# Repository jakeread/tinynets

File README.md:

# Tiny Nets

TinyNets presents a networking strategy for distributed robotic control systems. Resilient Stateless Multipath Message Passing for Very Fast Very Small Messages: RSMMRVFVSM ... 

## Networked Control Systems (NCS)

The field of Networked Control Systems, or NCS, is unique from many other networking fields. NCS refers to any application where many devices are linked together to perform control of a physical system. They are common in robotics and avionics, where many sensors and actuators work together to perform a common goal (i.e. walking, stabilization, etc.), and in manufacturing, where machine degrees of freedom are linked to close positioning control loops, and where multiple machines are linked to coordinate material handling and production scheduling. 

Critically,
- In NCS, **total throughput is valued but not a key metric.** 
- Rather, message sizes are typically very small (between three and fifty bytes) and message delay time is the critical metric. Often, messages are only one packet in length.  
- **Determinism in Message Delivery Time is critical** - systems must guarantee that certain control loops 'close' within a defined set of time less they become unstable. 
- **Robustness is critical** - NCS should not contain any Single Points of Failure
- **Statelessness is critical** - NCS should not pause operation under any circumstances to re-converge on routing solutions, as this adds fatal indeterminism to message delivery. 

## The State of the Art in NCS

State of the art Networked Control Systems employ simple Switched Ethernet, or proprietary versions thereof, in order to route traffic. Hardware endpoints are fitted with an Ethernet PHY and are connected in a heirarchy of switches. Ethernet MAC addresses are used, and all routing takes place on Layer 2. 

Switched Ethernet has become the industry standard because of its relative interoperability and high speeds. Critically, the last 10 years has seen Switched Ethernet take up large portions of market share because it solves many problems associated with Fieldbusses. Most importantly, adding devices to a Fieldbus always caused a linear increase in message delivery time, as is not the case with Switched Ethernet.

## Dissatisfaction with Switched Ethernet

However, Switched Ethernet was not originally developed for Networked Control Systems, and many in industry have pointed out that it will not fulfill customer needs in the near- and long-term future.

In Switched Ethernet, because a Minimum Spanning Tree is created, nodes in a particular layer compete for link-time on the layer above. Message delay time increases linearly with the probability that peers are transmitting at the same time, and with the number of peers on that layer. 

In addition, Switched Ethernet contains Single Points of Failure, where a broken link or switch means that the network must re-run the Spanning Tree Protocol algorithm - a process that often takes seconds. Because Switched Ethernet graphs are highly heirarchical, it is often the case that failure on a single link can cause entire sections of the network to fail, or become unreachable. 

Device endpoints in NCS are scaling down in size and up in number. Requiring that each endpoint carries with it an RJ45 Magnetic Jack and Ethernet PHY is dubious, and sets a lower limit on the size and complexity that sensors and actuators in an NCS must possess. 

Switched Ethernet is non-programmable. I.E. Switches are black-box IC's and do not allow systems designers to arbitrarily add functions to a system on the networking layer. For example, many NCS designers would like to implement message priorities and load balancing, but this is not possible on Layer 2. 

# Constraints and Cost Functions for TinyNet

## Constraints

In the design of TinyNets, we operate under the following constraints:

- TinyNet should be trivially integrated on device endpoints. I.E. an endpoint should not require any additional hardware circuitry. This allows the network to scale down into micro-robotics applications.
- TinyNets should run entirely in C or C++ on the processors used on endpoints and routers, meaning that network protocols can be openly modified within an Autonomous System to perform application-specific tasks. TinyNets is Open Source Software.
- TinyNets should run with no global state. It should not have to re-converge on routing solutions in the face of broken or modified links, additions to the network, or changes in traffic patterns.

## Direct Comparisons

It will be difficult to perform one-to-one comparisons between our network and the state of the art, as we are proposing a completely new solution in response to problems in NCS that we believe cannot be addressed with incremental modifications to existing technologies. 

## Proving our Merit

However, we can offer analysis as to why we believe our approach is substantially better than current offerings - or has a better problem-solution fit than other technologies. 

**Realtime / Convergence Free Multipath Routing in a Distance-Vector Routing Protocol**
- Existing Multipath Routing Technologies offer multipath routing (which eliminates the switching-bottleneck issues associated with switched ethernet), however, they do so using link-state routing that requires each router to share common knowledge about the complete network graph. In the face of link outages or router failures, networks must re-converge - a process that interrupts flows and causes massive increases, or complete failures, in message deliveries. For example
 - ECMP (Equal Cost Multipath Routing): more of a tool than an actual strategy; simply considers multiple paths when there are multiple best paths, i.e. load balancing mechanism
 - OSPF (Open Shortest Path First): Computes shortest path tree using Dijstra -- must know entire graph; wikipedia states convergence time is on the order of seconds (links to Cisco default parameters that set timeouts to be multiple seconds); specifically for Ethernet and offers a multipath version
 - SPB (Shortest Path Bridging): allows multiple equal cost paths and claims network is unaffected when a node fails except for the path(s) affected by the node failure, i.e. still cannot find another path if there is a unique shortest path containing a broken link
 - TRILL (TRansparent Interconnect of Lots of Links): must know entire graph, otherwise extremely similar to our protocol (uses hop counts and has similar flooding procedure); operates in Layer 2 and uses Fabric Shortest Path First (FSPF) to calculate alternate routes in node failure scenarios

We seek to demonstrate that these re-convergence times would cause operational failure in NCS, thus eliminating ECMP and OSPF as possible solutions to the NCS problem. 

The three protocols in question (OSPF, SPB, TRILL) require knowing the entire graph to perform a global shortest path calculation. All three of them allow for multipath consideration when there are multiple best paths. 200 ms seems to be the lower bound on convergence times as FSPF is quoted to having as good as 200 ms convergence time in the book "IBM SAN Solution Design Best Practices for VMWare" book. The vanilla OSPF protocol that Cisco offers indicates around an order second convergence time while optimized versions offer similar timing to FSPF (see paper).

200 ms sounds like a reasonable convergence time (and is quoted as being extremely fast) so to prove our merit, we need to demonstrate systems that do not have multiple shortest paths using the protocols above. This should highlight the main benefit of our protocol, that being the capability to perform real time alternate path calculations in a reasonable amount of time.

We propose designing multiple experiments to showcase the benefit of our protocol:
1. Grid structure network - test latency of corner communication and traffic of network during node failure. This test will serve as a control since there will be many shortest paths (if hop count is used as the metric).
2. Ring structure network - we already have graphs for this from the other protocol and it will demonstrate the speed at which each protocol finds the only other path in the event of a node failure.
3. Mesh network - fully connected network that will test our network utilization (ensure ringing doesn't happen or is at least bounded tightly). Test the latency of cross network communication in the event of a node failure. We should expect to see minimal decision time in our protocol and minimal flooding.

**Avoiding Switching Bottlenecks with Multipath Routing**
- In a careful literature review and analysis, we will show that Layer-2 Solutions (switched ethernet) necessarily cause switching bottlenecks that create Single Points of Failure and increases in Message Delivery Times to NCS.

From [worst-case-packet-delay-time paper], we know that the worst case communication delay over Ethernet occurs when the number of frames attempting to communicate over a single switch is the greatest. For example, when a spanning tree organizes itself such that 24 stations are connected to a single switching hub, a typical 144-bit message with a bit time of 0.1 us would take more than 1.5 ms to finish sending a single packet from all stations. If the packets could be interconnected without the tree structure required by Ethernet/IP, transmission time could be brought down to just over 300 us. 

The above figure compares strategies for reducing communication time. The parameter which has the largest parameter is the number of frames being communicated over a single switch. This is to be expected, since that parameter will have a multiplicative effect on the queuing delay. By sacrificing the spanning tree topology and leveraging multipath routing without the added processing delays and stateful nature of ECMP or other link-state routing methodologies, we will drastically reduce frame count and, therefore, communication time.

## Our Cost Functions

In addition to proving our merit with a careful literature review, we can devise cost functions and metrics to measure our development. These include:

**Optimal Network Utilization**
- Using logic analyzers and in-system programming to track message delay times and routes, we will measure the efforts of TinyNet routing policies to optimize network utilization and minimize message delivery times.

**Deterministic Packet Delivery in the face of Increasing Network Traffic**
- Similarly, we will measure TinyNet performance (in terms of message delivery times) as total network traffic increases.

**Robust Packet Delivery in the face of Lost Links and Routers**
- We will demonstrate TinyNet adaptively re-routing messages as links are cut, or routers are removed from the network graph, without any network re-convergence.  

# Key Contributions

A strategy for stateless multipath routing that increases message delivery time determinism and network robustness.

A real-time cost function, using next-hop buffer size (i.e. busyness metric) as well as historical hop-count for per-packet dynamic re-routing, that increases packet delivery-time determinism. 

A software-defined network architecture for arbitrary implementation in any embedded system, where computing, physical space, and time is limited. 

# Direct Applications

#### Micro-Robotics with Complexity

NCS via Switched Ethernet is impossible to drive into micro-robotics, where a single RJ45 Jack is larger than many endpoints. TinyNets provides a strategy and implementable software stack that will allow roboticists to bring adaptable, real-time networking to highly interconnected and complicated robotic systems. 

#### Avionics

Existing NCS are prone to Single Points of Failure and rapidly scaling complexity and cost. These is the bane of aircraft systems designers. We believe that TinyNet can offer avionics networks a robust, simple, and easily extensible strategy for the design and implementation of NCS in aircraft control systems. 

##### Open Source Reconfigurable Hardware Systems

In particular, hardware design for embedded systems in the open source (i.e. non-expert) realm. We want to offer a networking solution that allows open source designers to easily integrate their systems. We take the example of a proliferation of 3D Printer Control systems, none of which interop, and the interfaces between are a PITA. Expand on this. 

# TinyNet Protocol & Architecture

We develop a router, protocol and implementation of a network that: 
 - Implements a Multipath Distance-Vector Routing Protocol
 - Does Realtime Route Selection
 - Does Automatic, Convergence-free Route Discovery and Optimization
 - Is robust in the face of link losses and router failures
 - Can be arbitrarily implemented in software on numerous microcontrollers

## Addressing 
    - 10-bit address (1024 Unique in System, scalable by systems designers at the cost of larger packet size)
    - Addresses are assigned in software (Ethernet: Hardware Addresses)
    - Can be location-based (e.g. first five MSBs correspond to x, last five correspond to y)

## Packet Structure  

| Type | 8 Bits | 10 Bits | 6 Bits | 10 Bits | 6 Bits | N Bytes | CRC |  
| --- | --- | --- | --- | --- | --- | --- | --- | 
| Standard: | 255 | Dest. | Hop Count | Src. | # Bytes | Payload … | CRC |  
| ACK: | 253 | Dest. | Hop Count | Src. | x | x | CRC |  
| Buffer Length: | [0 - 251] | x | x | x | x | x | x |  

* previously-flooded Standard Packets have start delimiter 254
* previously-flooded Acks have start delimiter 252

## Routing Rules

On Packet Received:
```swift

if the packet is not a buffer update:
	update the LUT using packet src. and hop count

if packet is standard:
    if I am destination:
        process data in packet
		reply with ACK
    else:
		increment hop count
        if LUT has destination address:
            send packet to port which minimizes C(hops, buffer) = hops + \lambda*buffer over all ports
        else:
            send packet to all ports as standard flood

elseif packet is ack:
    if I am destination:
        process acknowledgement
    else:
        increment hop count
        if LUT has destination address:
            send packet to port which minimizes C(hops, buffer) = hops + \lambda*buffer over all ports
        else:
            send packet to all ports as ack flood

elseif packet is standard flood:
	remove packet src. from LUT at that port if it exists
	if I have not yet seen this flood:
		if I am destination:
			process data in packet
			reply with ACK
		else:
			increment hop count
			if LUT has destination address:
				send packet to port which minimizes C(hops, buffer) = hops + \lambda*buffer as standard packet
			else:
				send packet to all ports except one from which it was received

elseif packet is ack flood
    remove packet src. from LUT at that port if it exists
    if I am destination:
        process acknowledgement
    else:
		increment hop count
        if LUT has destination address:
            send packet to port which minimizes C(hops, buffer) = hops + \lambda*buffer as standard ACK
        else:
            send packet to all ports except one from which it was received

else:
    write buffer depth to LUT

```

## Routing Table

The routing table (or lookup table, LUT) consists of rows of:  

| Destination | Seen on Ports | Min. Hopcount Recorded on Port | Port buffer size |

This is different from standard Ethernet routing tables:

| Ports | Destinations seen on Port |

Because it includes the current port buffer size and number of hops as part of the table entry, allowing for a more robust cost function for use in the path planning algorithm. 

## Buffer Depth Updates
Send buffer depth on all ports every q seconds, and every time a packet leaves or arrives

## Announcements 
New arrivals to network do not announce, they simply begin transmitting. Their addresses are recoreded in surrounding switches' tables on their first packet-out.

## Withdrawals
Buffer Depth Updates are Periodic as well as event-based (on buffer-depth change). When no BDU is heard within a 250ms (or other setting) window, the node is considered withdrawn.

# Hardware

See /circuit 
See /embedded 

# Next Steps

Presents a good option for wired routing over robust networks, with some complexity pushed into the nodes. Only really advantageous when we want to be able to re-route messages upstream in order to move around bottlenecks. TN does load-balancing without thinking about it... other approaches would require some implementation. Perhaps there's a learning function for network path planning & routing? 

If we include flows, needs per-flow, not per-packet, routing - if we are going to hop about per buffers etc. 

Wants a C API for packetizing streams / flows. 

Still some question about duplicate message arrivals after message? OR don't packetize flows - add source -> destination 0-255 counter, only take next in this series. 

TN wins over the blissfully simple APA when we want a *very big* network, say, want 1,000,000 objects to individually address 1,000,000 objects. Here we also need to introduce heirarchichal addressing. 

'Napoleon's Messenger' 

APA is *loads* simpler to implement on FPGA

# Reading

#### Networked Control Systems
Ethernet in Networked Control, advantages and drawbacks.  
See especially  
**/litreview/papers/network-control-systems/survey-on-realtime-via-ethernet**  
**/litreview/papers/network-control-systems/the-emergence-of-networked-controls**  

##### Packet Delivery Times in the face of Increasing Network Traffic

~ plot w/ x-axis is # nodes, transmitting at some % of time, y axis is per-packet delivery time ~
~ graph is single branch / spanning tree

Critically, adding multi-path to the graph above decreases the slope of this plot. Twice the total link-time on the layer above is available, or Nx, where N is the number of nodes added to the next. 

* state of the art for this? there is lit review to do here - look up TRILL and SPB (shortest path bridging). Much of it comes from Data Center Networks. 
 - https://datacenteroverlords.com/2011/08/19/multi-path-ethernet-the-flying-cars-of-the-data-center/ 
 - http://ieeexplore.ieee.org/stamp/stamp.jsp?arnumber=6888840
 - https://en.wikipedia.org/wiki/Equal-cost_multi-path_routing
 - https://infoscience.epfl.ch/record/231114/files/main_nr.pdf

Also critically, *it seems that, in a cursory overview* many multi-path techniques in use today basically do dynamic spanning-tree rebuilds. These spanning-tree rebuilds have long convergence times (162ms is excitingly fast). 

However, to increase determinism routes need to be chosen dymanically - so that *very short timescale* changes can be made to a packet, mid-network-traverse, to route around busy switches. Of interest is finding evidence that this is not done in any existing system.

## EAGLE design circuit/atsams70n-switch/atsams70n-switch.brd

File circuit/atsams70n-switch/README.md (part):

# A Router for TinyNet

## Why

This is board for switching UART signals in TinyNet. I wanted to keep some track of what I was doing, while I was doing it. So here it is.

Originally, I had developed a switch on the XMEGA platform. I wanted to get into something a bit heavier duty, as I thought a really neat trick would be to out-perform switched ethernet, outright (for network control systems, not for datacenters). I think that in ARM chips there was enough speed to do this. Maximum UART bitrate is a function of the core clock speed (and in this case, the peripheral clock speed). I went straight to the 300MHz ATSAMx70 chips (M7 cores).

Now, being more prudent I would do some tests with these chips first, but I'm not going to. This is foolish, I know that. Max UART on the ATSAMS70 is clk/16, so 18.75Mbps. It's not huge (relative ethernet), but it's fast enough for realtime small messages on small systems. In any case, I think the question is about system architecture more than it is about outright performance at this point.

I also think that, for pure switching, an FPGA or PSOC would be a better answer. It probably is. I want to experiment with those during Networks week in [how to make](http://fab.cba.mit.edu/classes/863.17/CBA/people/jakeread/).

However, I also want my network switches to double-duty as motor controllers, sensor interfaces, etc - do general embedded-stuff. In another world, where infinite time exists, I would put FPGAs on board with a processor. With the FPGA comes a chance to invent a whole new PHY - w/ 'co-clocking' and auto-maxing bitrates, which is something I am still really interested in implementing, but there are also machines to build. I leave that experiment for another bench.

## The Chip

First order was picking the right Microcontroller for the job. I want a lot of things, and I expect this chip to become the heart of *much* of the work I'll do during the next two years, so the datasheet stakes have never been so high.

**I want a chip with: **
 - 5+ uarts
 - Big Clock Speed
 - DMA (direct memory access - peripherals write right into memory)
 - PWM's
 - ADC's
 - I2C
 - SPI
 - PIO (parallel input / output) is really exciting for communication

##### M7's

I ended up looking through Atmel's M4 and M7 Series of chips. These seem reasonably priced (actually cheap relative STM's). They're ARM, so the toolchain should be friendly to others. The M7's have a 300MHz clock that I'm getting childishly excited about.

My one issue is that they are a bit too fancy, and don't have exactly the peripherals I want. The XMEGAs have like 12 UARTS etc, the M7's max out at 5, even with 144 pins. 

I can also tell that programming these is going to be ... well ... less straightforward.

##### GO FOR
 - ATSAME70 - series - or ATSAMS70
  - E70 is 'industrial' - and S70 lacks an Ethernet Phy, but seems like it's way more popular...
 - oodles of peripherals
 - a chip you could drown in
 - 300MHz
 - did I mention peripherals?
 - $8 ... a good middle ground 

#### ATSAMS70N20
 - Exact PN  ATSAMS70N20A-AN 
 - N19: 512kb Flash, N20: 1024, N21: 2048
 - 300MHz
 - OOF: Need S70N-series for USART / SPI (has 100 pins :|)
 - Do LQFP for 14.5x14.5mm IC: TFBGA available, is 9x9mm
 - **Reads the datasheet**
  - print p. 1 -> 31 pins
  - print p. 77 -> 84 debug
  - p. 279 -> 346 clock / pmic
  - p. 346 -> 421 pio (gpio)
  - print p. 1093 -> 1117 uart
  - print p. 756 -> 788 spi
  - p. 831 -> 835 brief twi (i2c)
  - p. 964 - 968 brief usart
  - print p. 1178 -> 1186 -> 1282 pwm
  - p. 1283 -> 1288 afec (adc) brief
  - p. 158 -> 164 Power
  - p. 1554 -> 1574 Schematics

 - UART max clock is the Peripheral Clock or the PMC PCK - divided by 16. PMC PCK is an external clock, so UART clock can remain independent of processor clock.
 - So we can have (as measured) 22.8Mbps UART - into high-speed bouncy signal land. Exciting.

## Bonus Breakout

I want the following (or similar) pinouts coming off of the network node - to do *other stuff* with - i.e. motor control, sensing etc. Particularely, in a first rev of this board I am designing alongside my [bldc motor driver](https://gitlab.cba.mit.edu/jakeread/mkbldcdriver) project. 

 - 1x UART
 - 1x SPI w/ 4 cs, 1 for slave select
 - 1-2x i2c
 - 8-12x PWM, pairs three
 - all dac
 - 8-12 adc 

In the end, at this iteration, I have

 - 1 UART
 - 1 I2C (I2C and UART share one pin, so cannot be used at the same time)
 - 1 SPI w/ 2 Chip Selects
 - 1 USART w/ 2 Chip Selects (USART can be configured to do UART, or SPI, or a Clocked Serial line of your design)
 - 8 PWM's on 4 channels (hi/lo - this is designed for driving half bridges for motor control)
 - 4 Analog to Digital Converters (I am less pleased with this and want more...)
 - 3 Spare GPIO

Notes on this so far
 - More ADC's please
 - Pin headers could be split - to be breadboard friendly, and to offer some stability between layers

# Board Design

The first thing I did was to get into the datasheet. You can see that in the notes above. I am doing pinouts, figuring what I want on board. I am going to set this up as a kind of modular getdown, where the switch has a board interconnect, and I can build other PCBs w/ different hardwares to ride below. I.E motor controllers, sensor interfaces, human interfaces (!). Picking the set of pins I wanted to pull out of the chip was actually a bit painful. I'm sure I'll go through this more than once.

For JTAG Pinouts, I referenced the Tag-Connect footprint (available for download from Tag-Connect) and the ATSAM note here - http://www.atmel.com/webdoc/atmelice/atmelice.using_ocd_physical_jtag.html see Fig. 18. They match, so I don't have to do any footwork here. Nice.

I'm going to look at the board interconnect - to decide how many pins I want, I need to look at some applicaitons. I designed a Brushless Speed Controller last year, and this had me maxing out pins (for the first time!) I am going to use that as a starting point, and add I2C, which I know is common, and some other whatsits.

- 3v3
- GND (probably multiple - but want to keep clear signal / power GND separations. Alternately, spec for board-interconnect standoffs to do heavy ground lifting?
- PWM / GPIO x 18
- ADC x 6
- SPI x 2 x 2 CS (10)
- I2C (2) 
- DAC x 1
- Seems like 40 is right, ~ 41. 

I have been tempted to buy some fancy 'mezannine' connectors - but I ended up (after a few cycles) deciding to stick with a 2x20 2.54mm pitch connector. This way just about everyone will have access to the hardware, and I like that! It's also the same pitch as most IDC connectors, breadboards, etc - so hopping around between systems should be easy. I am almost tempted to split the pins a bit so that it could get right into a breadboard - or do an edge-style bb, but this seems like too much give in that direction.

OK, Here's my schematic

And the board

Fabricated

# Programming

It turns out this chip defaults to SWD, not JTAG. Should have read the datasheet more carefully. Also, I forgot to order the tag-connect for this number of pins...

### PIO

Here I am using the PIO peripheral (which also handles multiplexing for other peripherals) to turn one of my LED's on and off

```C

/*
 * atsams70-router.c
 *
 * Created: 11/18/2017 1:52:54 AM
 * Author : Jake
 */ 

#include "sam.h"

int main(void)
{
    // Initialize the SAM system
    SystemInit();
  
  // startup the PIOA peripheral clock - only necessary for Inputs and Interrupts
  PMC->PMC_PCER0 = 1 << ID_PIOA;
  
  // Peripheral Enable Register
  // Set PER to 1 at the pin to enable the PIO peripheral, 
  // set PDR (peripheral disable register) to 1 to clear that, opening the pin up for other peripherals (uart, etc)
  PIOA->PIO_PER |= PIO_PER_P28_Msk;
  // Output Enable Register
  PIOA->PIO_OER = PIO_PER_P28_Msk;

    while (1) 
    {
    // Clear Output Data Register (open drain)
    PIOA->PIO_CODR = PIO_PER_P28_Msk;
    // Set Output Data Register (voltage)
    PIOA->PIO_SODR = PIO_PER_P28_Msk;
    }
}

```

### ASF and Delay

ASF is Atmel Software Framework - from within Atmel Studio 7, ASF makes it easy to turn hardware peripherals on / off. It's kind of like a more-intense Arduino, in that it allows you to avoid digging in the Registers to do stuff. 

I'm more interested in doing the register digging, that way it seems easier to share and replicate code (no laundry list of dependencies to build and share) and it offers a future where I'm not in Atmel Studio 7, because *boo* proprietary software... 

But I do want a delay function, if only to test turning this light on and off. And, to be real, I think I want to use Atmel's USB CDC drivers as well - so that I can have a serial port enumerated real quick.

To use ASF, I also need to have a 'board' defined - this is like a hardware abstraction layer (HAL ... 9000). This is all explained as you go to ASF -> ASF Wizard in the top menu.

Now that I have this defined (a board) the build takes a LONG time. I am also getting a lot of errors, I think I'm going to start a new ASF project from scratch.

That's a lot better, I think.

To set the clock, I'm looking at 31.17 in the datasheet.

OK, F this, I went to http://asf.atmel.com/docs/latest/sam.drivers.mcan.quick_start.samv71_xplained_ultra/html/sysclk_quickstart.html and used ASF. I didn't need to configure anything other than setting up a #define BOARD_FREQ_MAINCK_XTAL (12000000UL) in my conf_board.h file. Nice. It's happily trucking at 300MHz now.

Here we are doing a GPIO Input

```C
#include <asf.h>

int main (void)
{
  /* Insert system clock initialization code here (sysclk_init()). */

  board_init();
  sysclk_init();
  
  /* Insert application code here, after the board has been initialized. */
  // startup the PIOA peripheral clock - only necessary for Inputs and Interrupts
  PMC->PMC_PCER0 = 1 << ID_PIOA;
  
  // Peripheral Enable Register
  // Set PER to 1 at the pin to enable the PIO peripheral,
  // set PDR (peripheral disable register) to 1 to clear that, opening the pin up for other peripherals (uart, etc)
  PIOA->PIO_PER |= PIO_PER_P28 | PIO_PER_P15;
  // Output Enable Register
  PIOA->PIO_OER = PIO_PER_P28;
  // Output Disable Register
  PIOA->PIO_ODR = PIO_PER_P15;
  // B1 pulls PA15 to GND

  while (1) {
    // Clear Output Data Register (open drain)
    if(PIOA->PIO_PDSR & PIO_PER_P15){
      PIOA->PIO_CODR = PIO_PER_P28;
    } else {
      PIOA->PIO_SODR = PIO_PER_P28;
    }
  }
}
```

### Ring Test

On the ring test, I'm getting a jumping value between 3.9MHz and 5.7MHz, 

pics

I'm hoping that the peripheral clock is set up on a different clock source than the main chip, as that's about 100 processor ticks between pin inversions, which is kind of unsatisfying.

So I couldn't find any way to change the clock frequency for PIO pins (although there are separate clocks for UART/USART and for the USB) but I did try putting the input on Port A and the Output on Port D, this put the ring back at 5.77MHz (173ns period). Here's the code I was running

```C

#include <asf.h>

// Ring is PD1 and PD2
// try PA17 and PD7

int main (void)
{
  /* Insert system clock initialization code here (sysclk_init()). */

  board_init();
  sysclk_init();
  
  /* Insert application code here, after the board has been initialized. */
  // startup the PIOA peripheral clock - only necessary for Inputs and Interrupts
  PMC->PMC_PCER0 = 1 << ID_PIOA;
  PMC->PMC_PCER0 = 1 << ID_PIOD; // to figure out what PCERx to write to, evaluate ID_yourperipheral, and look up on datashsheet p. 308 or 331
  
  // Peripheral Enable Register
  // Set PER to 1 at the pin to enable the PIO peripheral,
  // set PDR (peripheral disable register) to 1 to clear that, opening the pin up for other peripherals (uart, etc)
  PIOA->PIO_PER |= PIO_PER_P17; 
  PIOD->PIO_PER |= PIO_PER_P1 | PIO_PER_P2 | PIO_PER_P7;
  // Output Enable Register
  PIOA->PIO_OER = PIO_PER_P17;
  PIOD->PIO_OER = PIO_PER_P1;
  // Output Disable Register
  PIOD->PIO_ODR = PIO_PER_P7;
  PIOD->PIO_ODR = PIO_PER_P2;
  // B1 pulls PA15 to GND

  while (1) {
    if(REG_PIOD_PDSR & PIO_PER_P7){
      REG_PIOA_CODR = PIO_PER_P17;
    } else {
      REG_PIOA_SODR = PIO_PER_P17;
    }
  }
}
```

### UART

OK, now I'm going to go about setting up the UART, and see if I can push the bitrate *really* high.

Drove it up to 22.8 MHz (= 22.8 MBps) and saw some pretty gnar gnar ringing... I'm using a differential driver.

- pic 

I'm a little curious if it's maybe better to just drive right out of the logic level? It's a similar amount of bouncy... but with the differtial you take the difference, so ... in this photo Channel 2 (blue) is the logic level, and Channel 1 (yellow) is coming through the differential driver. I'm also curious if this can be chilled out with a tiny capacitor to ground... seems dubious. But in an exciting development I am into high speed signals land. Weeee. I would also be curious to see what a terminating resistor might do. I think, maybe not much? Update: basically this just attenuates the signal. My understanding is that terminating resistors (that span the + and - sides of the differential) are just meant to get rid of reflections.

- pic

Here's the barebones code I'm running

```C

#include <asf.h>

// P4LR is PD13
// Ring is PD1 and PD2
// try PA17 and PD7

// https://devel.rtems.org/browser/rtems/c/src/lib/libbsp/arm/atsam/libraries/libchip/source/uart.c?rev=e1eeb883d82ce218c2a9c754795cb3c86ac0f36d

int main (void)
{
  /* Insert system clock initialization code here (sysclk_init()). */

  board_init();
  sysclk_init();
  
  PMC->PMC_PCER0 = 1 << ID_PIOD;
  PIOD->PIO_OER = PIO_PER_P13;
  
  // P4RX -> URXD4 -> PD18
  // P4TX -> UTXD4 -> PD19
  
  PMC->PMC_PCER1 = 1 << 14; // ID is 44, position in this register is 12. datasheet p. 331 *shrugguy*
  
  // configure the pins for uart4
  // see datasheet 32.5.2 and 32.5.3
  PIOD->PIO_PDR = PIO_PER_P18; // see if we can combine once working
  PIOD->PIO_PDR = PIO_PER_P19;
  
  // we want peripheral c for both pins
  // abcdsr1 -> 0 abcdsr2 -> 1
  PIOD->PIO_ABCDSR[0] = ~PIO_PER_P18;
  PIOD->PIO_ABCDSR[0] = ~PIO_PER_P19;
  PIOD->PIO_ABCDSR[1] = PIO_PER_P18;
  PIOD->PIO_ABCDSR[1] = PIO_PER_P19;
  
  // set uart mode
  UART4->UART_MR = UART_MR_BRSRCCK_PERIPH_CLK | UART_MR_CHMODE_NORMAL;
  
  // set uart clock
  UART4->UART_BRGR = 1; // is selected clock / this*16
  
  // turn tx and rx on on the uart4 module
  UART4->UART_CR = UART_CR_TXEN | UART_CR_RXEN;

  while (1) {
    while(!(UART4->UART_SR & UART_SR_TXRDY)){
      PIOD->PIO_CODR = PIO_PER_P13;
    }
    PIOD->PIO_SODR = PIO_PER_P13;
    UART4->UART_THR = 85;
  }
}
```

OK, enough for that wakeup, now I'm going to try to boot the USB CDC driver. This is something I'm more stoked about, and the last key component to letting me know that these chips are going to generally work.

### USB CDC

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
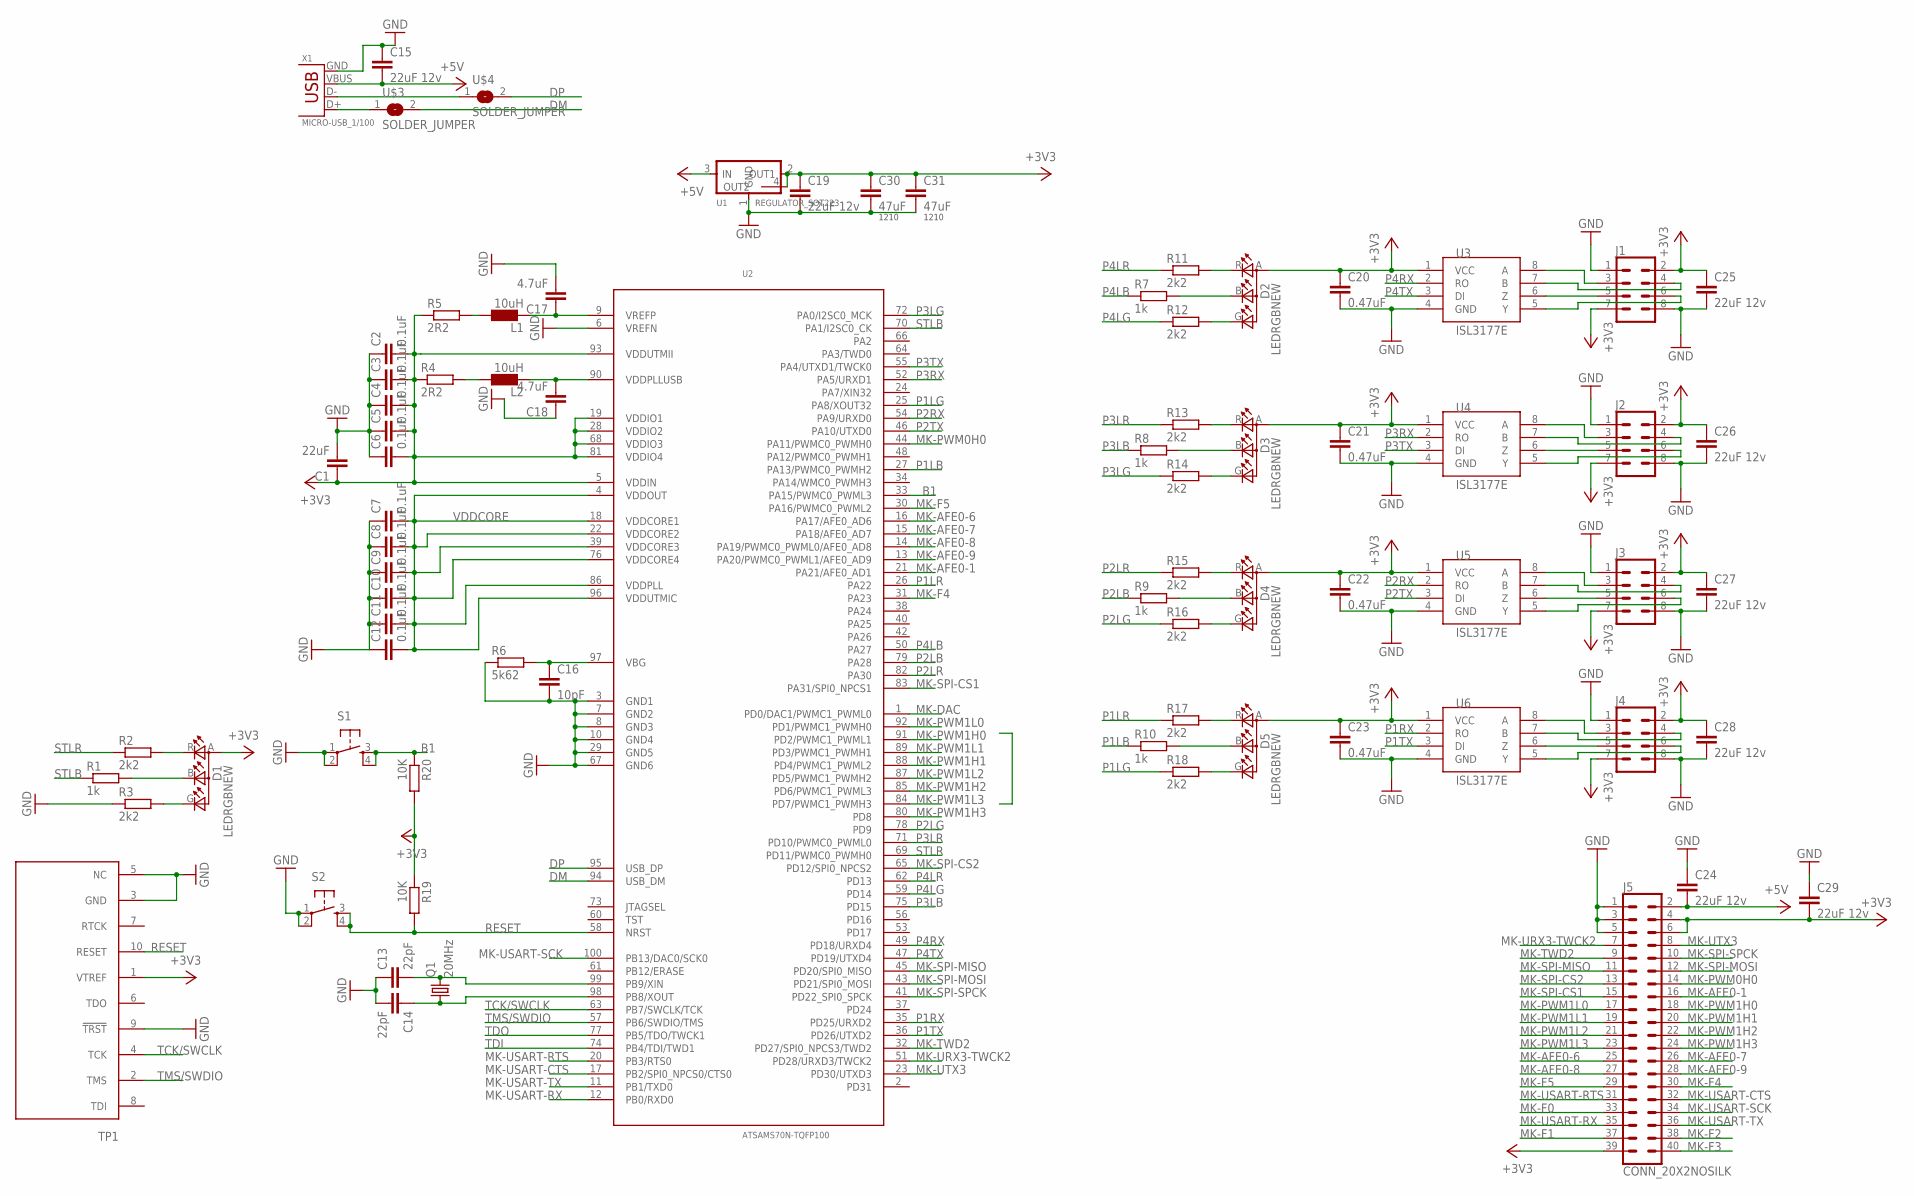
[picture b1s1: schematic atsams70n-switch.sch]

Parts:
C1: 22uF; C0805
C2, C3, C4, C5, C6, C7, C8, C9, C10, C11, C12: 0.1uF; C0603
C13, C14: 22pF; C0603
C15, C19, C24, C25, C26, C27, C28, C29: 22uF 12v; C0805
C16: 10pF; C0805
C17, C18: 4.7uF; C0805
C20, C21, C22, C23: 0.47uF; C0805
C30, C31: 47uF; 1210
D1, D2, D3, D4, D5: LEDRGBNEW; P-LCC-4
J1, J2, J3, J4: CONN_04X2SHROUDED; 2X4-SHROUDED
J5: CONN_20X2NOSILK; 2X20_NOSILK
L1, L2: 10uH; L1812
Q1: 20MHz; CTS406
R1, R7, R8, R9, R10: 1k; R0805
R2, R3, R11, R12, R13, R14, R15, R16, R17, R18: 2k2; R0805
R4, R5: 2R2; R0805
R6: 5k62; R0805
R19, R20: 10K; R0805
S1, S2: 6MM_SWITCH6MM_SWITCH; 6MM_SWITCH
TP1: TC2050-NL; TC2050-MCP
U1: REGULATOR_SOT223; SOT223
U2: ATSAMS70N-TQFP100; TQFP100-14X14
U3, U4, U5, U6: ISL3177E; MSOP8
U$3, U$4: SOLDER_JUMPER; SJFAB
X1: MICRO-USB_1/100; DX4R005HJ5_100

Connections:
+3V3: C1.1, C2.2, C3.2, C4.2, C5.2, C6.2, C19.1, C20.1, C21.1, C22.1, C23.1, C25.1, C26.1, C27.1, C28.1, C29.2, C30.1, C31.1, D1.A (A2), D2.A (A2), D3.A (A2), D4.A (A2), D5.A (A2), J1.2, J1.7, J2.2, J2.7, J3.2, J3.7, J4.2, J4.7, J5.4, J5.6, J5.39, R4.1, R5.1, R19.1, R20.2, TP1.1 (VTREF), U1.2 (OUT1), U1.4 (OUT2), U2.5 (VDDIN), U2.19 (VDDIO1), U2.28 (VDDIO2), U2.68 (VDDIO3), U2.81 (VDDIO4), U2.93 (VDDUTMII), U3.1 (VCC), U4.1 (VCC), U5.1 (VCC), U6.1 (VCC)
+5V: C15.2, C24.2, J5.2, U1.3 (IN), X1.VBUS
B1: R20.1, S1.3 (S), S1.4 (S1), U2.33 (PA15/PWMC0_PWML3)
DM: U2.94 (USB_DM), U$3.2
DP: U2.95 (USB_DP), U$4.2
GND: C1.2, C2.1, C3.1, C4.1, C5.1, C6.1, C7.1, C8.1, C9.1, C10.1, C11.1, C12.1, C13.1, C14.2, C15.1, C16.2, C17.2, C18.1, C19.2, C20.2, C21.2, C22.2, C23.2, C24.1, C25.2, C26.2, C27.2, C28.2, C29.1, C30.2, C31.2, J1.1, J1.8, J2.1, J2.8, J3.1, J3.8, J4.1, J4.8, J5.1, J5.3, J5.5, R3.1, R6.1, S1.1, S1.2 (P1), S2.1, S2.2 (P1), TP1.3 (GND), TP1.5 (NC), TP1.9 (!TRST), U1.1 (GND), U2.3 (GND1), U2.6 (VREFN), U2.7 (GND2), U2.8 (GND3), U2.10 (GND4), U2.29 (GND5), U2.67 (GND6), U3.4 (GND), U4.4 (GND), U5.4 (GND), U6.4 (GND), X1.GND
MK-AFE0-1: J5.16, U2.21 (PA21/AFE0_AD1)
MK-AFE0-6: J5.25, U2.16 (PA17/AFE0_AD6)
MK-AFE0-7: J5.26, U2.15 (PA18/AFE0_AD7)
MK-AFE0-8: J5.27, U2.14 (PA19/PWMC0_PWML0/AFE0_AD8)
MK-AFE0-9: J5.28, U2.13 (PA20/PWMC0_PWML1/AFE0_AD9)
MK-DAC: U2.1 (PD0/DAC1/PWMC1_PWML0)
MK-F0: J5.33
MK-F1: J5.37
MK-F2: J5.38
MK-F3: J5.40
MK-F4: J5.30, U2.31 (PA23)
MK-F5: J5.29, U2.30 (PA16/PWMC0_PWML2)
MK-PWM0H0: J5.14, U2.44 (PA11/PWMC0_PWMH0)
MK-PWM1H0: J5.18, U2.91 (PD2/PWMC1_PWML1)
MK-PWM1H1: J5.20, U2.88 (PD4/PWMC1_PWML2)
MK-PWM1H2: J5.22, U2.85 (PD6/PWMC1_PWML3)
MK-PWM1H3: J5.24, U2.80 (PD8)
MK-PWM1L0: J5.17, U2.92 (PD1/PWMC1_PWMH0)
MK-PWM1L1: J5.19, U2.89 (PD3/PWMC1_PWMH1)
MK-PWM1L2: J5.21, U2.87 (PD5/PWMC1_PWMH2)
MK-PWM1L3: J5.23, U2.84 (PD7/PWMC1_PWMH3)
MK-SPI-CS1: J5.15, U2.83 (PA31/SPI0_NPCS1)
MK-SPI-CS2: J5.13, U2.65 (PD12/SPI0_NPCS2)
MK-SPI-MISO: J5.11, U2.45 (PD20/SPI0_MISO)
MK-SPI-MOSI: J5.12, U2.43 (PD21/SPI0_MOSI)
MK-SPI-SPCK: J5.10, U2.41 (PD22_SPI0_SPCK)
MK-TWD2: J5.9, U2.32 (PD27/SPI0_NPCS3/TWD2)
MK-URX3-TWCK2: J5.7, U2.51 (PD28/URXD3/TWCK2)
MK-USART-CTS: J5.32, U2.17 (PB2/SPI0_NPCS0/CTS0)
MK-USART-RTS: J5.31, U2.20 (PB3/RTS0)
MK-USART-RX: J5.35, U2.12 (PB0/RXD0)
MK-USART-SCK: J5.34, U2.100 (PB13/DAC0/SCK0)
MK-USART-TX: J5.36, U2.11 (PB1/TXD0)
MK-UTX3: J5.8, U2.23 (PD30/UTXD3)
unnamed: D5.R (CRED), R17.2
unnamed: D5.B (CBLUE), R10.2
unnamed: D5.G (CGREEN), R18.2
unnamed: C13.2, Q1.3 (2), U2.99 (PB9/XIN)
unnamed: C14.1, Q1.1, U2.98 (PB8/XOUT)
unnamed: U$4.1, X1.D-
unnamed: C16.1, R6.2, U2.97 (VBG)
unnamed: L2.1, R4.2
unnamed: L1.1, R5.2
unnamed: C18.2, L2.2, U2.90 (VDDPLLUSB)
unnamed: C17.1, L1.2, U2.9 (VREFP)
unnamed: D1.R (CRED), R2.2
unnamed: J3.3, U5.8 (A)
unnamed: J3.4, U5.7 (B)
unnamed: J3.5, U5.6 (Z)
unnamed: J3.6, U5.5 (Y)
unnamed: D4.R (CRED), R15.2
unnamed: D4.B (CBLUE), R9.2
unnamed: D4.G (CGREEN), R16.2
unnamed: J2.3, U4.8 (A)
unnamed: J2.4, U4.7 (B)
unnamed: J2.5, U4.6 (Z)
unnamed: J2.6, U4.5 (Y)
unnamed: D3.R (CRED), R13.2
unnamed: J4.3, U6.8 (A)
unnamed: J4.4, U6.7 (B)
unnamed: J4.5, U6.6 (Z)
unnamed: J4.6, U6.5 (Y)
unnamed: D3.B (CBLUE), R8.2
unnamed: D3.G (CGREEN), R14.2
unnamed: J1.3, U3.8 (A)
unnamed: J1.4, U3.7 (B)
unnamed: J1.5, U3.6 (Z)
unnamed: J1.6, U3.5 (Y)
unnamed: D2.R (CRED), R11.2
unnamed: D2.B (CBLUE), R7.2
unnamed: D2.G (CGREEN), R12.2
unnamed: D1.B (CBLUE), R1.2
unnamed: D1.G (CGREEN), R3.2
unnamed: U$3.1, X1.D+
P1LB: R10.1, U2.27 (PA13/PWMC0_PWMH2)
P1LG: R18.1, U2.25 (PA8/XOUT32)
P1LR: R17.1, U2.26 (PA22)
P1RX: U2.35 (PD25/URXD2), U6.2 (RO)
P1TX: U2.36 (PD26/UTXD2), U6.3 (DI)
P2LB: R9.1, U2.79 (PA28)
P2LG: R16.1, U2.78 (PD9)
P2LR: R15.1, U2.82 (PA30)
P2RX: U2.54 (PA9/URXD0), U5.2 (RO)
P2TX: U2.46 (PA10/UTXD0), U5.3 (DI)
P3LB: R8.1, U2.75 (PD15)
P3LG: R14.1, U2.72 (PA0/I2SC0_MCK)
P3LR: R13.1, U2.71 (PD10/PWMC0_PWML0)
P3RX: U2.52 (PA5/URXD1), U4.2 (RO)
P3TX: U2.55 (PA4/UTXD1/TWCK0), U4.3 (DI)
P4LB: R7.1, U2.50 (PA27)
P4LG: R12.1, U2.59 (PD14)
P4LR: R11.1, U2.62 (PD13)
P4RX: U2.49 (PD18/URXD4), U3.2 (RO)
P4TX: U2.47 (PD19/UTXD4), U3.3 (DI)
RESET: R19.2, S2.3 (S), S2.4 (S1), TP1.10 (RESET), U2.58 (NRST)
STLB: R1.1, U2.70 (PA1/I2SC0_CK)
STLR: R2.1, U2.69 (PD11/PWMC0_PWMH0)
TCK/SWCLK: TP1.4 (TCK), U2.63 (PB7/SWCLK/TCK)
TDI: U2.74 (PB4/TDI/TWD1)
TDO: U2.77 (PB5/TDO/TWCK1)
TMS/SWDIO: TP1.2 (TMS), U2.57 (PB6/SWDIO/TMS)
VDDCORE: C7.2, C8.2, C9.2, C10.2, C11.2, C12.2, U2.4 (VDDOUT), U2.18 (VDDCORE1), U2.22 (VDDCORE2), U2.39 (VDDCORE3), U2.76 (VDDCORE4), U2.86 (VDDPLL), U2.96 (VDDUTMIC)

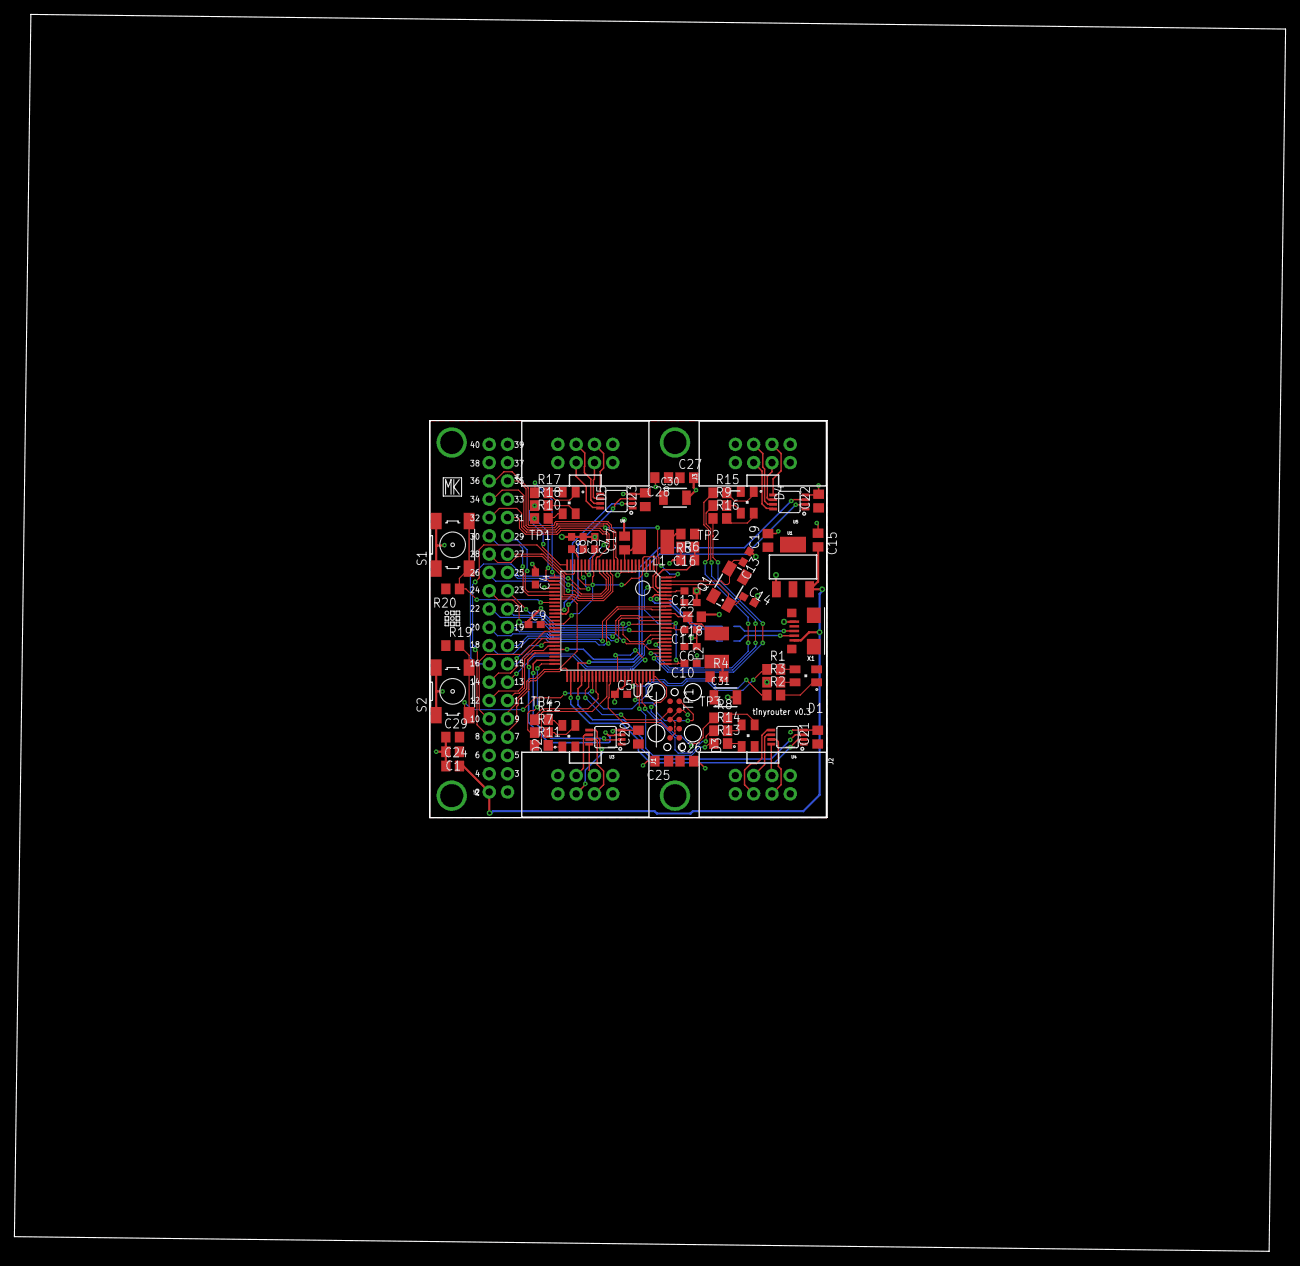
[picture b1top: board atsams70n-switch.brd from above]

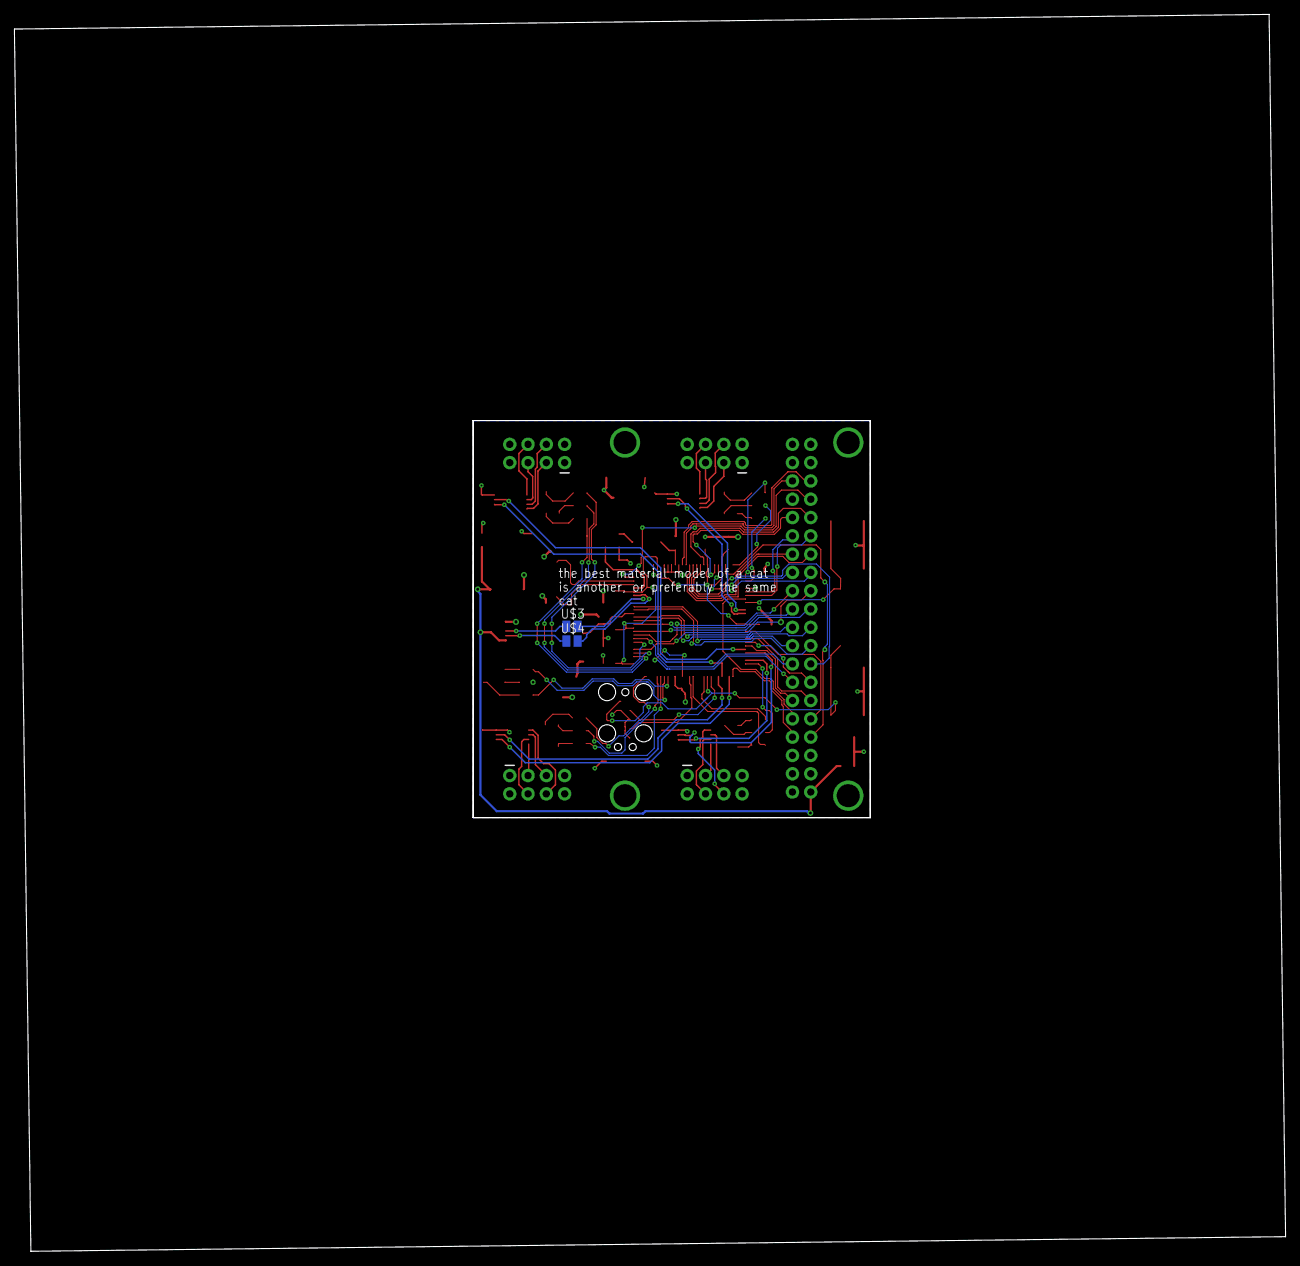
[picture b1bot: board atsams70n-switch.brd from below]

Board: 2 copper layers, 176.5 x 171.7 mm, 78 parts (2 on the bottom side), 101 nets.

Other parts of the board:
U$1: MK-LOGO-SILK
U$2: CBA-SILK-LOGO

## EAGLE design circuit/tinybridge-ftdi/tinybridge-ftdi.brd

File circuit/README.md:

# A Router for TinyNet

## Why

This is board for switching UART signals in TinyNet. I wanted to keep some track of what I was doing, while I was doing it. So here it is.

Originally, I had developed a switch on the XMEGA platform. I wanted to get into something a bit heavier duty, as I thought a really neat trick would be to out-perform switched ethernet, outright (for network control systems, not for datacenters). I think that in ARM chips there was enough speed to do this. Maximum UART bitrate is a function of the core clock speed (and in this case, the peripheral clock speed). I went straight to the 300MHz ATSAMx70 chips (M7 cores).

Now, being more prudent I would do some tests with these chips first, but I'm not going to. This is foolish, I know that. Max UART on the ATSAMS70 is clk/16, so 18.75Mbps. It's not huge (relative ethernet), but it's fast enough for realtime small messages on small systems. In any case, I think the question is about system architecture more than it is about outright performance at this point.

I also think that, for pure switching, an FPGA or PSOC would be a better answer. It probably is. I want to experiment with those during Networks week in [how to make](http://fab.cba.mit.edu/classes/863.17/CBA/people/jakeread/).

However, I also want my network switches to double-duty as motor controllers, sensor interfaces, etc - do general embedded-stuff. In another world, where infinite time exists, I would put FPGAs on board with a processor. With the FPGA comes a chance to invent a whole new PHY - w/ 'co-clocking' and auto-maxing bitrates, which is something I am still really interested in implementing, but there are also machines to build. I leave that experiment for another bench.

## The Chip

First order was picking the right Microcontroller for the job. I want a lot of things, and I expect this chip to become the heart of *much* of the work I'll do during the next two years, so the datasheet stakes have never been so high.

**I want a chip with: **
 - 5+ uarts
 - Big Clock Speed
 - DMA (direct memory access - peripherals write right into memory)
 - PWM's
 - ADC's
 - I2C
 - SPI
 - PIO (parallel input / output) is really exciting for communication

##### M7's

I ended up looking through Atmel's M4 and M7 Series of chips. These seem reasonably priced (actually cheap relative STM's). They're ARM, so the toolchain should be friendly to others. The M7's have a 300MHz clock that I'm getting childishly excited about.

My one issue is that they are a bit too fancy, and don't have exactly the peripherals I want. The XMEGAs have like 12 UARTS etc, the M7's max out at 5, even with 144 pins. 

I can also tell that programming these is going to be ... well ... less straightforward.

##### GO FOR
 - ATSAME70 - series - or ATSAMS70
  - E70 is 'industrial' - and S70 lacks an Ethernet Phy, but seems like it's way more popular...
 - oodles of peripherals
 - a chip you could drown in
 - 300MHz
 - did I mention peripherals?
 - $8 ... a good middle ground 

#### ATSAMS70N20
 - Exact PN  ATSAMS70N20A-AN 
 - N19: 512kb Flash, N20: 1024, N21: 2048
 - 300MHz
 - OOF: Need S70N-series for USART / SPI (has 100 pins :|)
 - Do LQFP for 14.5x14.5mm IC: TFBGA available, is 9x9mm
 - **Reads the datasheet**
  - print p. 1 -> 31 pins
  - print p. 77 -> 84 debug
  - p. 279 -> 346 clock / pmic
  - p. 346 -> 421 pio (gpio)
  - print p. 1093 -> 1117 uart
  - print p. 756 -> 788 spi
  - p. 831 -> 835 brief twi (i2c)
  - p. 964 - 968 brief usart
  - print p. 1178 -> 1186 -> 1282 pwm
  - p. 1283 -> 1288 afec (adc) brief
  - p. 158 -> 164 Power
  - p. 1554 -> 1574 Schematics

 - UART max clock is the Peripheral Clock or the PMC PCK - divided by 16. PMC PCK is an external clock, so UART clock can remain independent of processor clock.
 - So we can have (as measured) 22.8Mbps UART - into high-speed bouncy signal land. Exciting.

## Bonus Breakout

I want the following (or similar) pinouts coming off of the network node - to do *other stuff* with - i.e. motor control, sensing etc. Particularely, in a first rev of this board I am designing alongside my [bldc motor driver](https://gitlab.cba.mit.edu/jakeread/mkbldcdriver) project. 

 - 1x UART
 - 1x SPI w/ 4 cs, 1 for slave select
 - 1-2x i2c
 - 8-12x PWM, pairs three
 - all dac
 - 8-12 adc 

In the end, at this iteration, I have

 - 1 UART
 - 1 I2C (I2C and UART share one pin, so cannot be used at the same time)
 - 1 SPI w/ 2 Chip Selects
 - 1 USART w/ 2 Chip Selects (USART can be configured to do UART, or SPI, or a Clocked Serial line of your design)
 - 8 PWM's on 4 channels (hi/lo - this is designed for driving half bridges for motor control)
 - 4 Analog to Digital Converters (I am less pleased with this and want more...)
 - 3 Spare GPIO

Notes on this so far
 - More ADC's please
 - Pin headers could be split - to be breadboard friendly, and to offer some stability between layers

# Board Design

The first thing I did was to get into the datasheet. You can see that in the notes above. I am doing pinouts, figuring what I want on board. I am going to set this up as a kind of modular getdown, where the switch has a board interconnect, and I can build other PCBs w/ different hardwares to ride below. I.E motor controllers, sensor interfaces, human interfaces (!). Picking the set of pins I wanted to pull out of the chip was actually a bit painful. I'm sure I'll go through this more than once.

For JTAG Pinouts, I referenced the Tag-Connect footprint (available for download from Tag-Connect) and the ATSAM note here - http://www.atmel.com/webdoc/atmelice/atmelice.using_ocd_physical_jtag.html see Fig. 18. They match, so I don't have to do any footwork here. Nice.

I'm going to look at the board interconnect - to decide how many pins I want, I need to look at some applicaitons. I designed a Brushless Speed Controller last year, and this had me maxing out pins (for the first time!) I am going to use that as a starting point, and add I2C, which I know is common, and some other whatsits.

- 3v3
- GND (probably multiple - but want to keep clear signal / power GND separations. Alternately, spec for board-interconnect standoffs to do heavy ground lifting?
- PWM / GPIO x 18
- ADC x 6
- SPI x 2 x 2 CS (10)
- I2C (2) 
- DAC x 1
- Seems like 40 is right, ~ 41. 

I have been tempted to buy some fancy 'mezannine' connectors - but I ended up (after a few cycles) deciding to stick with a 2x20 2.54mm pitch connector. This way just about everyone will have access to the hardware, and I like that! It's also the same pitch as most IDC connectors, breadboards, etc - so hopping around between systems should be easy. I am almost tempted to split the pins a bit so that it could get right into a breadboard - or do an edge-style bb, but this seems like too much give in that direction.

OK, Here's my schematic

And the board

Fabricated

## Bill of Materials

| Part | Value | Package | Number | PN | 
| --- | --- | --- | --- | ---- |
| C | 0.1uF | 0603 | 11 | - |
| C | 22pF | 0603 | 2 | - |
| C | 10pF | 0805 | 1 | - |
| C | 0.47uF | 0805 | 4 | - |
| C | 4.7uF | 0805 | 2 | - |
| C | 22uF 16V | 0805 | 9 | - |
| C | 47uF 16V | 1210 | 2 | - |
| R | 2R2 | 0805 | 2 | - |
| R | 1K | 0805 | 5 | - |
| R | 2K2 | 0805 | 10 | - |
| R | 5K62 | 0805 | 1 | - |
| R | 10K | 0805 | 2 | - |
| L | 10uH | 1812 | 2 | - |
| Q | 12MHz | CT406 | 1 | - |
| D | LEDRGBNEW | P-LCC-4 | 5 | - |
| U | ISL3177E | MSOP8 | 4 | - |
| U | ATSAMS70N | TQFP100 | 1 | - |
| U | 3V3 Reg | SOT223 | 1 | - |
| Connector | 02x04 Shrouded | - | 4 | - |
| Switch | FAB Momentary | - | 2 | - |

## Incremental

next board
 - tiny inductor filters on vddpll and vddoutmic, maybe shield usb, as this might work?
 - if end of term / long time span, do v71 for usb dreams?

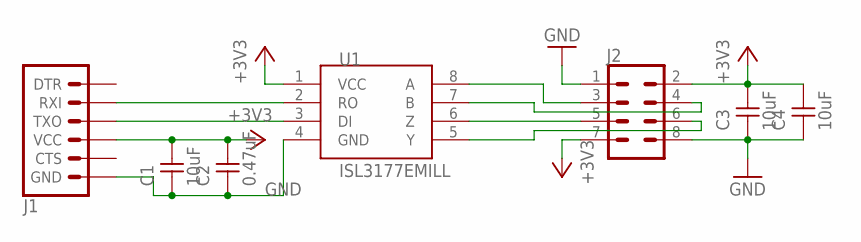
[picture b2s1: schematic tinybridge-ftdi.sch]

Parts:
C1, C3, C4: 10uF; C1206
C2: 0.47uF; C1206
J1: 6_PIN_SERIAL_TARGETMILLING; 1X06-SQUISH
J2: CONN_04X2SHROUDED-SQUISH; 2X4-SHROUDED-SQUISH
U1: ISL3177EMILL; MSOP8-8MILPADS

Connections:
+3V3: C1.2, C2.2, C3.2, C4.2, J1.4 (VCC), J2.2, J2.7, U1.1 (VCC)
GND: C1.1, C2.1, C3.1, C4.1, J1.6 (GND), J2.1, J2.8, U1.4 (GND)
unnamed: J1.2 (RXI), U1.2 (RO)
unnamed: J1.3 (TXO), U1.3 (DI)
unnamed: J2.3, U1.8 (A)
unnamed: J2.4, U1.7 (B)
unnamed: J2.5, U1.6 (Z)
unnamed: J2.6, U1.5 (Y)

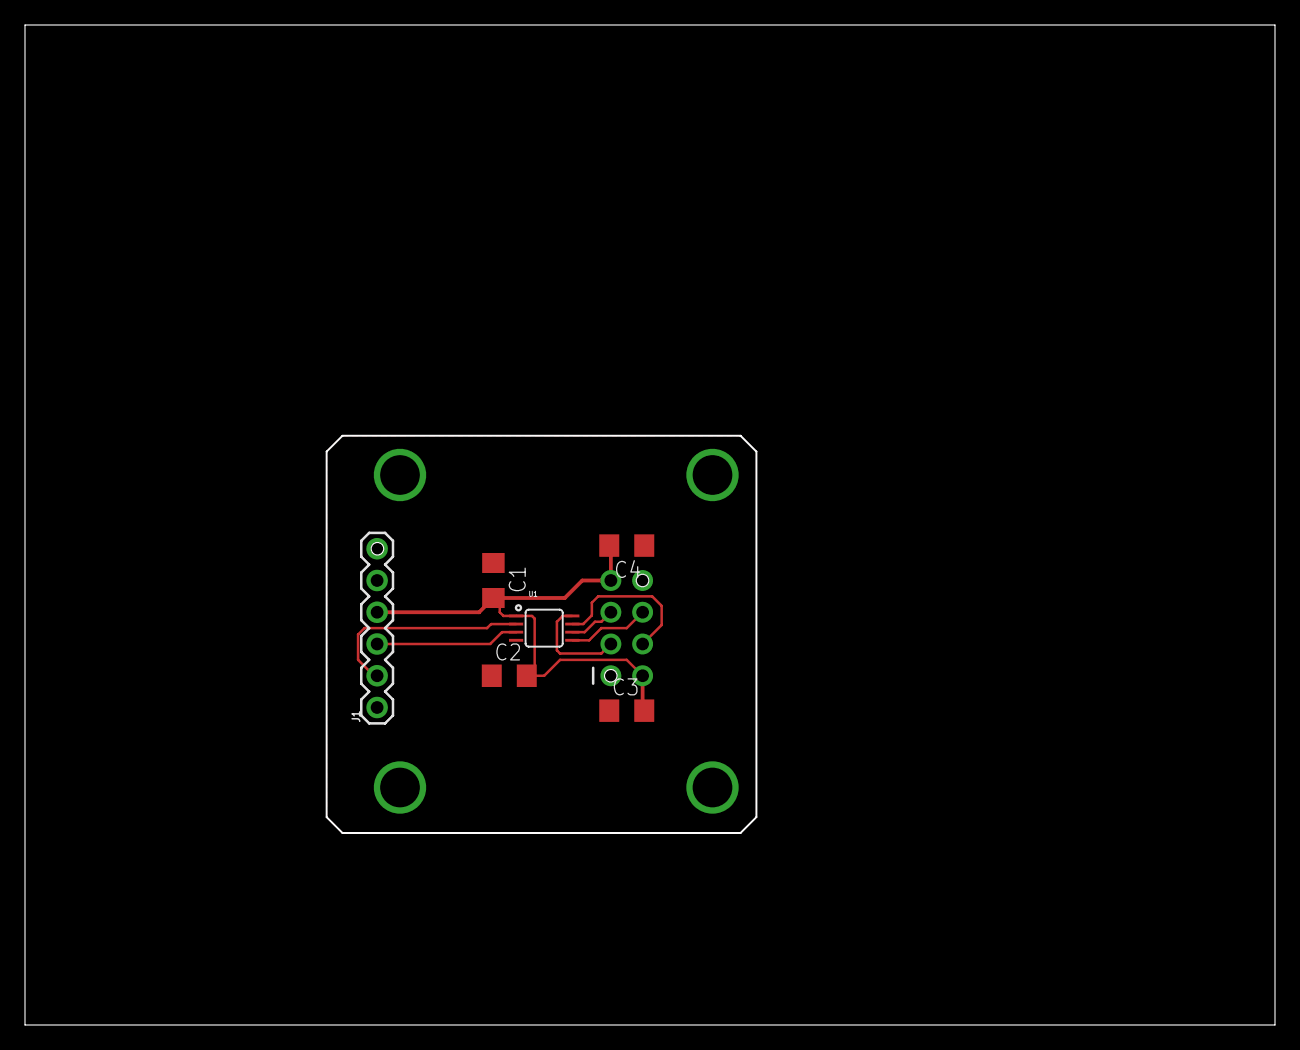
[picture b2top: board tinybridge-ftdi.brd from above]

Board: 2 copper layers, 100.0 x 80.0 mm, 7 parts (1 on the bottom side), 8 nets.

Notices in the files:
parts and their libraries:
SparkFun-Connectors: Licensing: Creative Commons ShareAlike 4.0 International - https://creativecommons.org/licenses/by-sa/4.0
tag-connect-2050: ©2009 ROFA.cz
